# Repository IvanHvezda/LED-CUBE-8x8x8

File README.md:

# LED kostka 8×8×8

Maturitní práce, SPŠ na Proseku, obor Elektrotechnika, 2024.
512 LED diod, vlastní deska plošného spoje navržená v KiCadu,
ovládání mobilní aplikací MIT App Inventor přes Bluetooth.

**▶ [Video ukázka](https://youtu.be/GqQKeZAHj2E)**

---

## Obsah repozitáře

- **[Elektrická část](Elektrick%C3%A1%20%C4%8D%C3%A1st/)** — KiCad projekt, schéma, blokové schéma, návrh DPS, seznam součástek, fotky elektroniky
- **[Konstrukce](Konstrukce/)** — fotky hotové konstrukce
- **[Program](Program/)** — kód hvezdiv20: hlavní `.ino` soubor, hlavičkové `.h` soubory, vývojový diagram
- **[Aplikace](Aplikace/)** — blokový program, prostředí aplikace
- **[Média](M%C3%A9dia/)** — Obrázky

Textová část maturitní práce leží přímo v kořeni repozitáře:

- [Maturitní práce (PDF)](hvezdiv20.pdf)
- [Maturitní práce (DOCX)](hvezdiv20.docx)
- [Popis zip souboru](Popis%20zip%20souboru.txt)

---

## Co to umí

- 29 zobrazovacích funkcí — animace deště, 3D matrix, rotující krychle, padající kapky
- zobrazení času a data (RTC modul), teploty a vlhkosti (čidlo DHT)
- výpis textu zadaného v aplikaci — psaním nebo hlasem
- režim náhodných animací
- signalizační LED stavu spárování

## Technické řešení

| | |
| --- | --- |
| Řídicí jednotka | Arduino Mega 2560 |
| Zobrazovač | 512× červená LED 5 mm, matice 8×8×8 |
| Řízení sloupců | 8× posuvný registr SN74HC595 (64 sloupců, 24 datových pinů) |
| Řízení vrstev | 8 digitálních pinů přímo z Arduina |
| Multiplex | po vrstvách, střída 1/8 |
| Komunikace | UART → Bluetooth modul HC-05 |
| Senzory | DHT (teplota, vlhkost), RTC modul reálného času |
| Napájení a data | konektor USB-B (VCC, GND, RX, TX), pojistka 400 mA |
| Deska | dvouvrstvá, návrh v KiCadu |
| Konstrukce | dřevěná skříň, kryt z plexiskla, krytí IP20 |
| Rozměry | 260 × 260 × 380 mm |

## Proč Arduino Mega

Vybíral jsem mezi Raspberry Pi Zero, ESP32 a Arduinem Mega podle čtyř
kritérií: počet pinů, velikost paměti, programovací jazyk a cena.
Raspberry Zero mělo nejvíc paměti i integrovaný Bluetooth, ale
znamenalo by naučit se Python v době, kdy jsem potřeboval hlavně dodat
funkční zařízení. ESP32 vypadalo dobře, ale tehdy jsem ho vyřadil kvůli
počtu pinů — dnes vím, že se u něj piny dají přemapovat, takže to
rozhodnutí stálo na mojí neznalosti. Arduino Mega nabídlo 54 pinů
a dostatečnou paměť za cenu externího Bluetooth modulu.

## Jak funguje adresování

Matice je rozdělená na 64 sloupců a 8 vrstev. Rozsvícení konkrétní
diody znamená nastavit její sloupec a její vrstvu — funguje to jako
souřadnice. Posuvné registry umožnily ovládat 64 sloupců pouhými
24 datovými piny.... 8 x (data, latch, clock) místo 64.

## Co bych dnes udělal jinak

**Buzení vrstev.** Osm vrstev spínám přímo digitálními piny Arduina.
Při rozsvícené vrstvě tak jedním pinem teče proud všech 64 diod dané
vrstvy — ATmega2560 má přitom doporučeno 20 mA na pin a absolutní
maximum 40 mA. Návrh tedy nemá žádnou rezervu: jakmile bych proud
na diodu zvýšil na běžných 10 mA, pinem by teklo přes půl ampéru
a zničilo by ho to.

Naměřený odběr celé kostky při plném rozsvícení je 152 mA, což
odpovídá zlomkům miliampéru na diodu. Proud tedy neurčuje návrh,
ale kombinace sériových rezistorů a sdílené cesty do země přes
společný pin vrstvy. Přesně to není spočítané.

Správné řešení: MOSFETy na spínání vrstev.

Mechanika. Vodiče mezi deskou a LED konstrukcí jsem navrhl příliš
krátké, takže se při manipulaci uvolňovaly z konektorů a občas
nesvítil celý sloupec. Delší vodiče a zajištěné konektory.

Software. Původně jsem měl přes 7000 řádků v jediném souboru.
Rozdělení do hlavičkových souborů — jedna funkce na soubor a společný
`variables.h` — byla nejlepší změna v celém projektu. Dnes bych
od začátku napsal framework pro definici animací, aby se nová funkce
dala popsat jako poloha diod v čase, ne jako vlastní logika.
Software má obrovské množství možností, ale omezuje mě paměť, 
proto bych přidal SD karta modul nebo jinou externí paměť, třeba 
EEPROM paměť AT24C256. Potom by se na kostce dala naprogramovat jednoduchá 3D hra,
třeba 3D tetris nebo 3D snake.

## Plán do budoucna

Rozšířit projekt na LED kostku 32x32x32.

Ivan Hvězda · free.hvezda.lance@gmail.com

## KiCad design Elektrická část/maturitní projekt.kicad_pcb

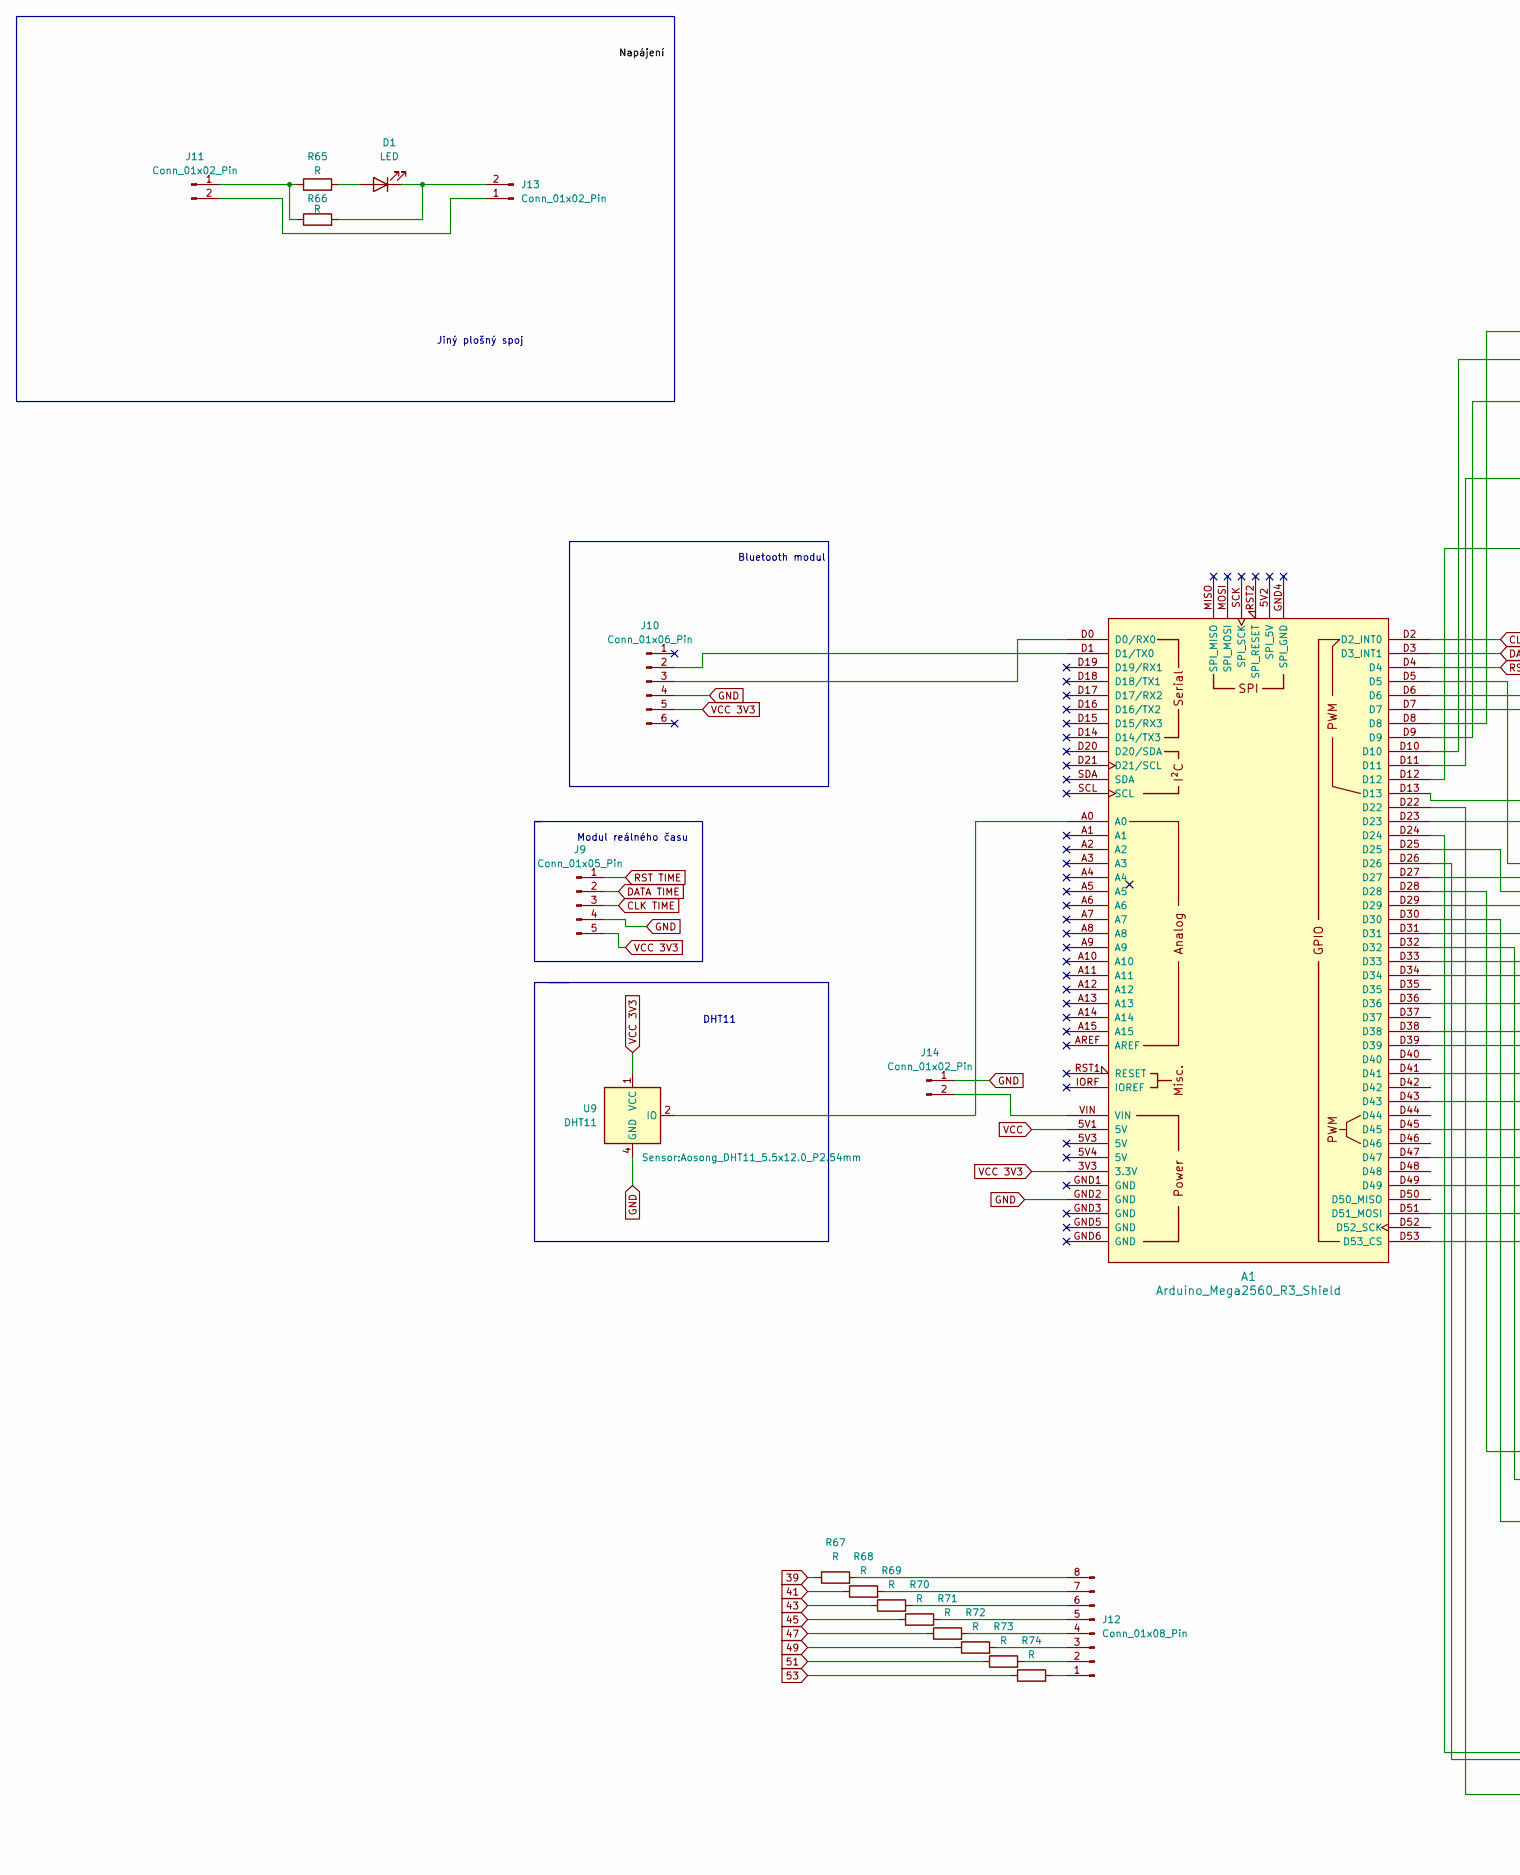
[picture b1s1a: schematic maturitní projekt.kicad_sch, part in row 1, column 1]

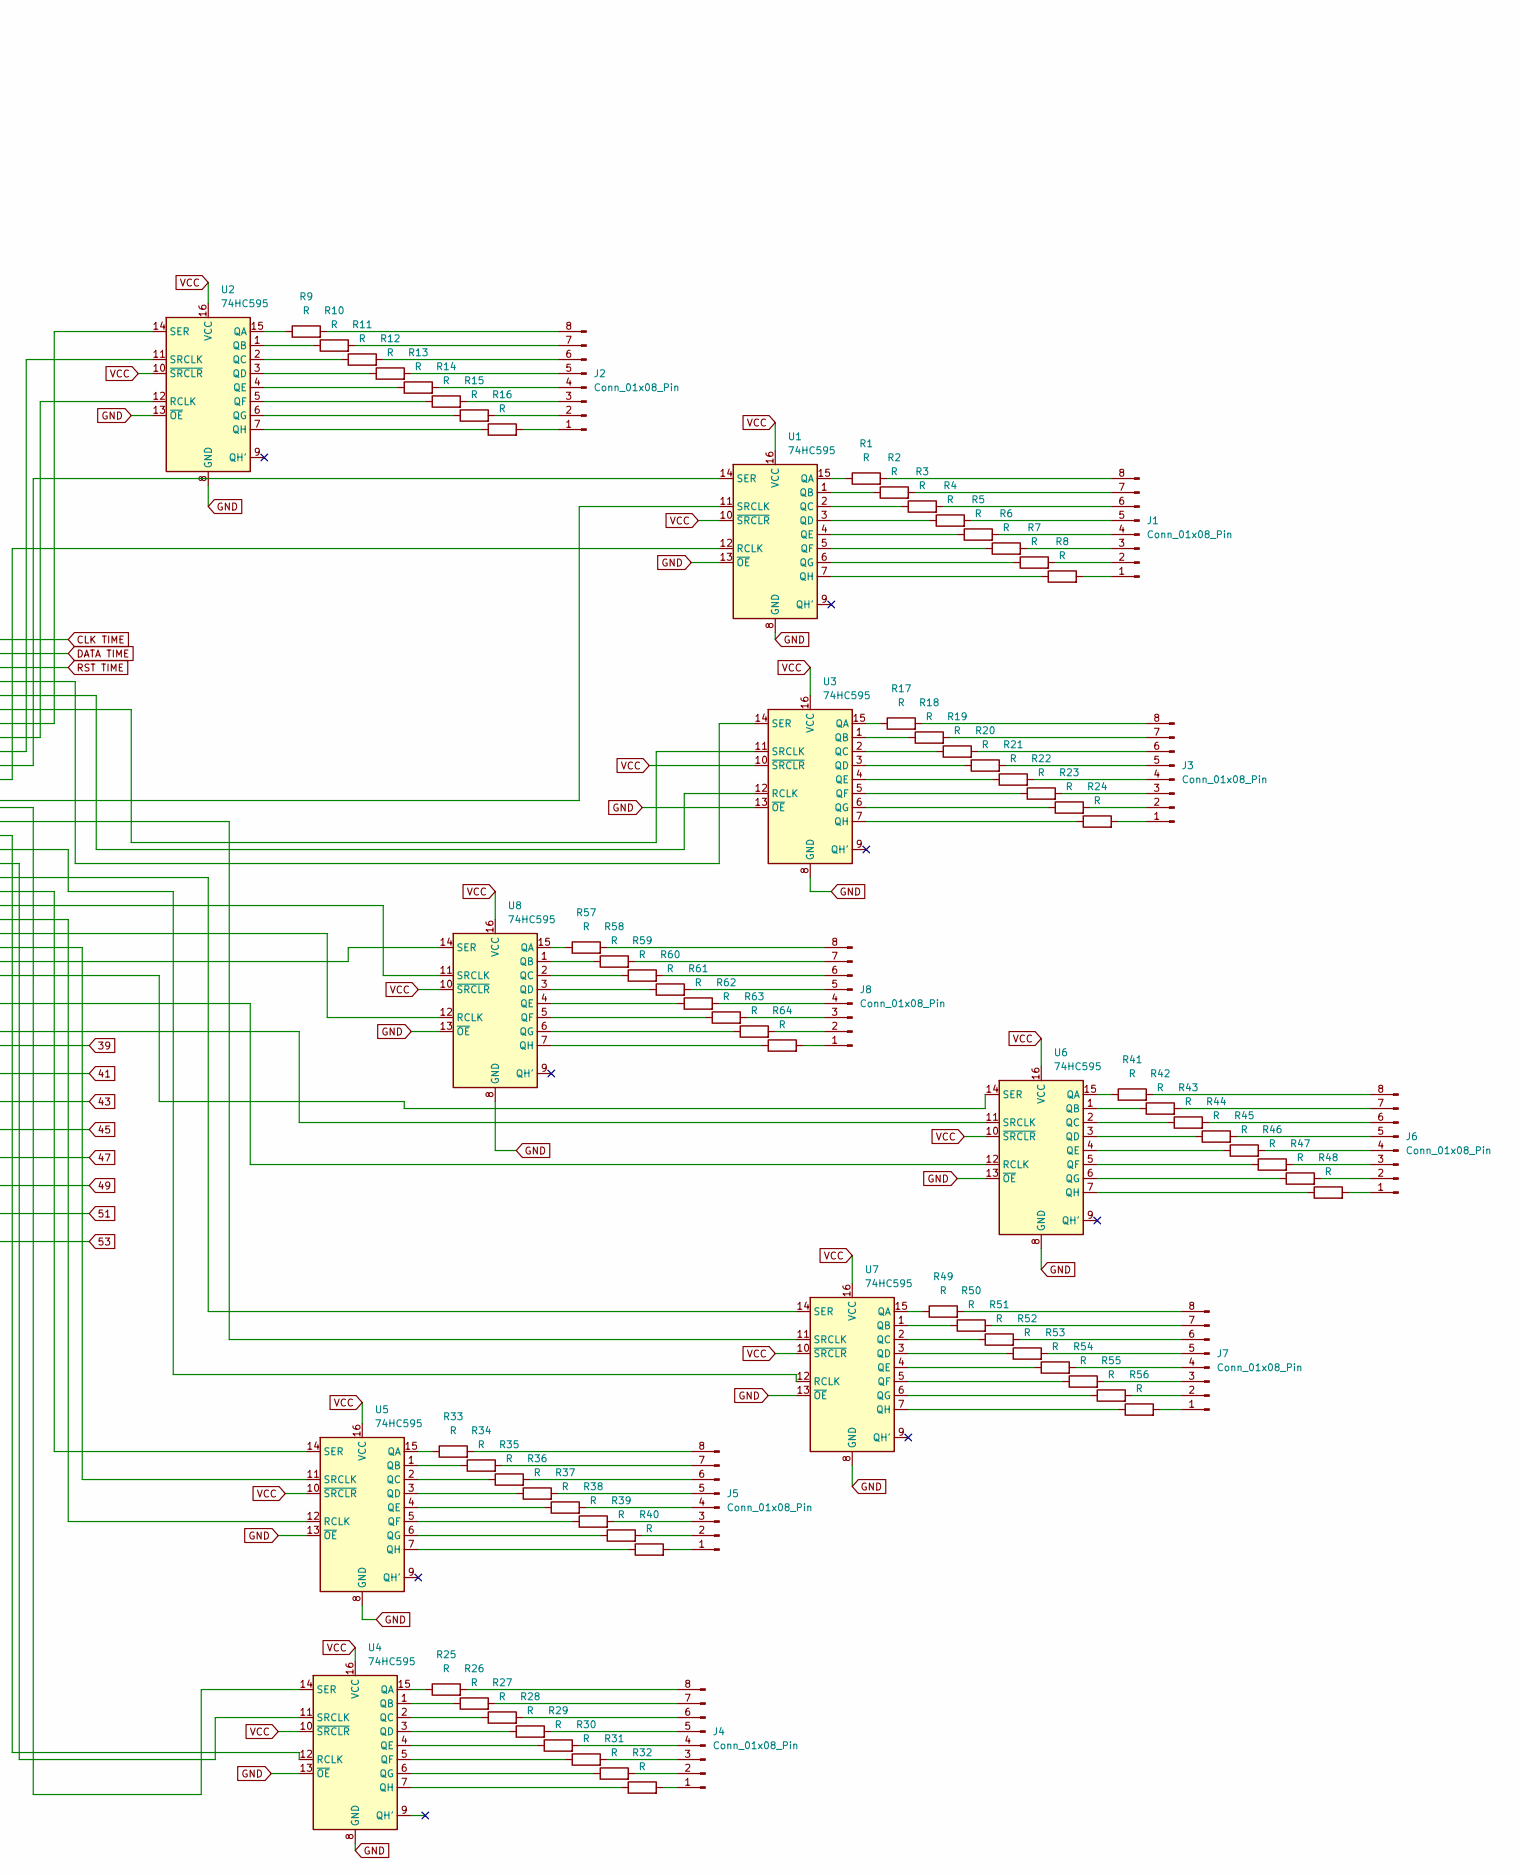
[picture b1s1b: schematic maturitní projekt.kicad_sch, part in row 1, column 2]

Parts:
A1: Arduino_Mega2560_R3_Shield
D1: LED; Napájení
J1, J2, J3, J4, J5, J6, J7, J8, J12: Conn_01x08_Pin; PinHeader_1x08_P2.54mm_Vertical
J9: Conn_01x05_Pin; ds1302
J10: Conn_01x06_Pin; Bluetooth
J11, J13, J14: Conn_01x02_Pin; Napájení
R1, R2, R3, R4, R5, R6, R7, R8, R9, R10, R11, R12, R13, R14, R15, R16, R17, R18, R19, R20, R21, R22, R23, R24, R25, R26, R27, R28, R29, R30, R31, R32, R33, R34, R35, R36, R37, R38, R39, R40, R41, R42, R43, R44, R45, R46, R47, R48, R49, R50, R51, R52, R53, R54, R55, R56, R57, R58, R59, R60, R61, R62, R63, R64, R65, R66, R67, R68, R69, R70, R71, R72, R73, R74: R; R_Axial_DIN0207_L6.3mm_D2.5mm_P10.16mm_Horizontal
U1, U2, U3, U4, U5, U6, U7, U8: 74HC595; 74hc595n
U9: DHT11; Aosong_DHT11_5.5x12.0_P2.54mm

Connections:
39: A1.D39, R67.1
41: A1.D41, R68.1
43: A1.D43, R69.1
45: A1.D45, R70.1
47: A1.D47, R71.1
49: A1.D49, R72.1
51: A1.D51 (D51_MOSI), R73.1
53: A1.D53 (D53_CS), R74.1
CLK TIME: A1.D2 (D2_INT0), J9.3
DATA TIME: A1.D3 (D3_INT1), J9.2
GND: A1.GND2 (GND), J9.4, J10.4, J14.1, U1.8 (GND), U1.13 (~OE), U2.8 (GND), U2.13 (~OE), U3.8 (GND), U3.13 (~OE), U4.8 (GND), U4.13 (~OE), U5.8 (GND), U5.13 (~OE), U6.8 (GND), U6.13 (~OE), U7.8 (GND), U7.13 (~OE), U8.8 (GND), U8.13 (~OE), U9.4 (GND)
unnamed: A1.D0 (D0/RX0), J10.3
unnamed: A1.D1 (D1/TX0), J10.2
unnamed: D1.1 (K), J13.2, R66.2
unnamed: D1.2 (A), R65.2
unnamed: J1.1, R8.2
unnamed: J1.2, R7.2
unnamed: J1.3, R6.2
unnamed: J1.4, R5.2
unnamed: J1.5, R4.2
unnamed: J1.6, R3.2
unnamed: J1.7, R2.2
unnamed: J1.8, R1.2
unnamed: J2.1, R16.2
unnamed: J2.2, R15.2
unnamed: J2.3, R14.2
unnamed: J2.4, R13.2
unnamed: J2.5, R12.2
unnamed: J2.6, R11.2
unnamed: J2.7, R10.2
unnamed: J2.8, R9.2
unnamed: J3.1, R24.2
unnamed: J3.2, R23.2
unnamed: J3.3, R22.2
unnamed: J3.4, R21.2
unnamed: J3.5, R20.2
unnamed: J3.6, R19.2
unnamed: J3.7, R18.2
unnamed: J3.8, R17.2
unnamed: J4.1, R32.2
unnamed: J4.2, R31.2
unnamed: J4.3, R30.2
unnamed: J4.4, R29.2
unnamed: J4.5, R28.2
unnamed: J4.6, R27.2
unnamed: J4.7, R26.2
unnamed: J4.8, R25.2
unnamed: J5.1, R40.2
unnamed: J5.2, R39.2
unnamed: J5.3, R38.2
unnamed: J5.4, R37.2
unnamed: J5.5, R36.2
unnamed: J5.6, R35.2
unnamed: J5.7, R34.2
unnamed: J5.8, R33.2
unnamed: J6.1, R48.2
unnamed: J6.2, R47.2
unnamed: J6.3, R46.2
unnamed: J6.4, R45.2
unnamed: J6.5, R44.2
unnamed: J6.6, R43.2
unnamed: J6.7, R42.2
unnamed: J6.8, R41.2
unnamed: J7.1, R56.2
unnamed: J7.2, R55.2
unnamed: J7.3, R54.2
unnamed: J7.4, R53.2
unnamed: J7.5, R52.2
unnamed: J7.6, R51.2
unnamed: J7.7, R50.2
unnamed: J7.8, R49.2
unnamed: J8.1, R64.2
unnamed: J8.2, R63.2
unnamed: J8.3, R62.2
unnamed: J8.4, R61.2
unnamed: J8.5, R60.2
unnamed: J8.6, R59.2
unnamed: J8.7, R58.2
unnamed: J8.8, R57.2
unnamed: J11.1, R65.1, R66.1
unnamed: J11.2, J13.1
unnamed: J12.1, R74.2
unnamed: J12.2, R73.2
unnamed: J12.3, R72.2
unnamed: J12.4, R71.2
unnamed: J12.5, R70.2
unnamed: J12.6, R69.2
unnamed: J12.7, R68.2
unnamed: J12.8, R67.2
unnamed: A1.VIN, J14.2
unnamed: R1.1, U1.15 (QA)
unnamed: R2.1, U1.1 (QB)
unnamed: R3.1, U1.2 (QC)
unnamed: R4.1, U1.3 (QD)
unnamed: R5.1, U1.4 (QE)
unnamed: R6.1, U1.5 (QF)
unnamed: R7.1, U1.6 (QG)
unnamed: R8.1, U1.7 (QH)
unnamed: A1.D12, U1.12 (RCLK)
unnamed: A1.D11, U1.14 (SER)
unnamed: A1.D13, U1.11 (SRCLK)
unnamed: R9.1, U2.15 (QA)
unnamed: R10.1, U2.1 (QB)
unnamed: R11.1, U2.2 (QC)
unnamed: R12.1, U2.3 (QD)
unnamed: R13.1, U2.4 (QE)
unnamed: R14.1, U2.5 (QF)
unnamed: R15.1, U2.6 (QG)
unnamed: R16.1, U2.7 (QH)
unnamed: A1.D9, U2.12 (RCLK)
unnamed: A1.D8, U2.14 (SER)
unnamed: A1.D10, U2.11 (SRCLK)
unnamed: R17.1, U3.15 (QA)
unnamed: R18.1, U3.1 (QB)
unnamed: R19.1, U3.2 (QC)
unnamed: R20.1, U3.3 (QD)
unnamed: R21.1, U3.4 (QE)
unnamed: R22.1, U3.5 (QF)
unnamed: R23.1, U3.6 (QG)
unnamed: R24.1, U3.7 (QH)
unnamed: A1.D6, U3.12 (RCLK)
unnamed: A1.D5, U3.14 (SER)
unnamed: A1.D7, U3.11 (SRCLK)
unnamed: R25.1, U4.15 (QA)
unnamed: R26.1, U4.1 (QB)
unnamed: R27.1, U4.2 (QC)
unnamed: R28.1, U4.3 (QD)
unnamed: R29.1, U4.4 (QE)
unnamed: R30.1, U4.5 (QF)
unnamed: R31.1, U4.6 (QG)
unnamed: R32.1, U4.7 (QH)
unnamed: A1.D24, U4.12 (RCLK)
unnamed: A1.D22, U4.14 (SER)
unnamed: A1.D26, U4.11 (SRCLK)
unnamed: R33.1, U5.15 (QA)
unnamed: R34.1, U5.1 (QB)
unnamed: R35.1, U5.2 (QC)
unnamed: R36.1, U5.3 (QD)
unnamed: R37.1, U5.4 (QE)
unnamed: R38.1, U5.5 (QF)
unnamed: R39.1, U5.6 (QG)
unnamed: R40.1, U5.7 (QH)
unnamed: A1.D30, U5.12 (RCLK)
unnamed: A1.D28, U5.14 (SER)
unnamed: A1.D32, U5.11 (SRCLK)
unnamed: R41.1, U6.15 (QA)
unnamed: R42.1, U6.1 (QB)
unnamed: R43.1, U6.2 (QC)
unnamed: R44.1, U6.3 (QD)
unnamed: R45.1, U6.4 (QE)
unnamed: R46.1, U6.5 (QF)
unnamed: R47.1, U6.6 (QG)
unnamed: R48.1, U6.7 (QH)
unnamed: A1.D36, U6.12 (RCLK)
unnamed: A1.D34, U6.14 (SER)
unnamed: A1.D38, U6.11 (SRCLK)
unnamed: R49.1, U7.15 (QA)
unnamed: R50.1, U7.1 (QB)
unnamed: R51.1, U7.2 (QC)
unnamed: R52.1, U7.3 (QD)
unnamed: R53.1, U7.4 (QE)
unnamed: R54.1, U7.5 (QF)
unnamed: R55.1, U7.6 (QG)
unnamed: R56.1, U7.7 (QH)
unnamed: A1.D25, U7.12 (RCLK)
unnamed: A1.D27, U7.14 (SER)
unnamed: A1.D23, U7.11 (SRCLK)
unnamed: R57.1, U8.15 (QA)
unnamed: R58.1, U8.1 (QB)
unnamed: R59.1, U8.2 (QC)
unnamed: R60.1, U8.3 (QD)
unnamed: R61.1, U8.4 (QE)
unnamed: R62.1, U8.5 (QF)
unnamed: R63.1, U8.6 (QG)
unnamed: R64.1, U8.7 (QH)
unnamed: A1.D31, U8.12 (RCLK)
unnamed: A1.D33, U8.14 (SER)
unnamed: A1.D29, U8.11 (SRCLK)
unnamed: A1.A0, U9.2 (IO)
RST TIME: A1.D4, J9.1
VCC: A1.5V1 (5V), U1.10 (~SRCLR), U1.16 (VCC), U2.10 (~SRCLR), U2.16 (VCC), U3.10 (~SRCLR), U3.16 (VCC), U4.10 (~SRCLR), U4.16 (VCC), U5.10 (~SRCLR), U5.16 (VCC), U6.10 (~SRCLR), U6.16 (VCC), U7.10 (~SRCLR), U7.16 (VCC), U8.10 (~SRCLR), U8.16 (VCC)
VCC 3V3: A1.3V3 (3.3V), J9.5, J10.5, U9.1 (VCC)

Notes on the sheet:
DHT11
Bluetooth modul
Jiný plošný spoj
Modul reálného času

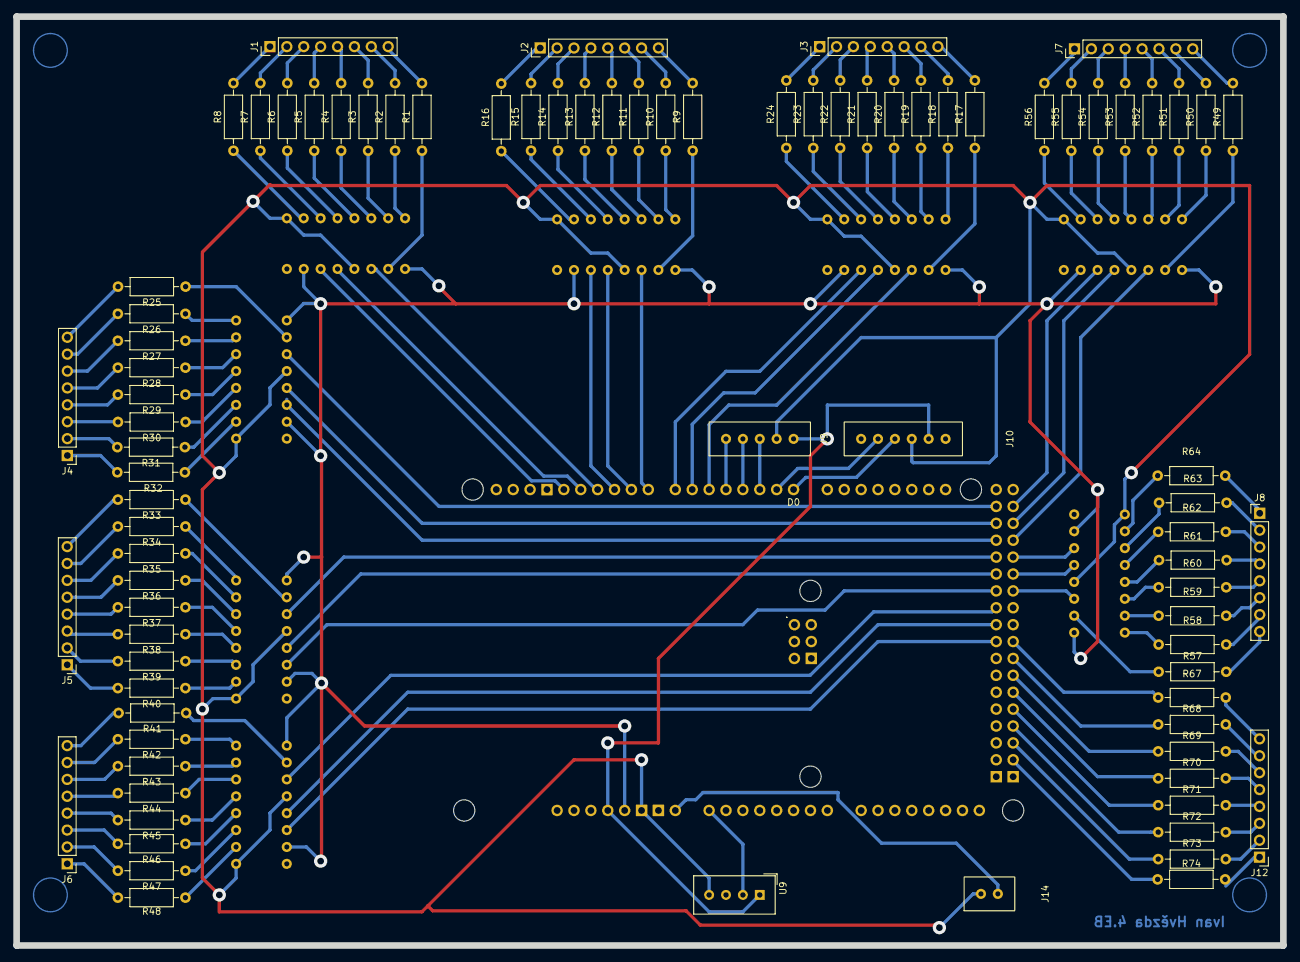
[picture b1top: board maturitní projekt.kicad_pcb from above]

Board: 2 copper layers, 190.5 x 139.7 mm, 94 parts (0 on the bottom side), 178 nets.
